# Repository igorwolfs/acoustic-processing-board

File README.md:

# acoustic-processing-hw
Repository for the main FPGA-processing board of my acoustic characterization device.

## Design goal
The goal of the board is to 
1. Measure analog signals amplified by a [pre-amplifier board](https://github.com/igorwolfs/acoustic-preamp-hw) for signals picked up from the piezo, at frequencies between 0.1 and 10 MHz. These analog signals are stored in RAM after measurement, processed on the FPGA and passed on.
2. Drive PWM signals for a [single-phase inverter-board](https://github.com/igorwolfs/acoustic-piezodriver-hw) connected to a piezo-element.

## Design constraints
Apart from technical constraints such as sampling rate (> 20 MHz), transfer / processing speed (10-bit x 35 MHz), etc... The main design constraint was keeping the price as low as possible.

## Stackup / Routing
6-layer stackup (JLC06161H-3313) with 
- L1, L6: controlled impedance layers.
	- 50 Ohm non-coplanar microstrip: 
		- TL Width (W): 0.157 mm 
		- Spacing between conductors: 2-3 x W
	- 100 Ohm differential non-coplanar
		- TL width (W): 0.122 mm
		- Diff-pair spacing: 0.2032 mm
		- Conductor spacing: 2-3 x W
- L4: power plane:
	- +2V5 Auxiliary FPGA voltage
	- +1V35 LPDDR3 voltage
	- +1V2 ETH voltage
	- +3V3 digital
	- +3V3 analog
- L2, L3, L5: GND planes
	- L2 (L1 reference)
	- L3 (L4 reference)
	- L5 (L6 reference)

### Rationale
Main reason for choosing a 6-layer over an 8-layer stack-up was price. Keeping LPDDR3-traces at appropriate impedance and matching delays proved to be a challenge with this layer count. Outcome to be judged after bringup.

## Main IC's
- Lattice EC5U-FPGA, with 25k LUT's.
- LPDDR3-RAM
- USB 33200-PHY (ULPI-bus)
- Ethernet PHY (RGMII interface)
- Analog frontend with MS9280 ADC in diff-mode, (fs <=35 MHz).

### Routing / Selection Rationale
#### Lattice ECP5U
The Lattice ECP5U was the best price-quality in terms of computing power. 

With a max CLK frequency of about 400 MHz it can operate around the lowest DDR3 speed class.

#### KSZ9031RN-Ethernet
Often used in open-source boards together with the ECP5U.

- RGMII interface operating at 125 MHz
- Differential pair needs to be tightly matched, offset calibration between pairs is performed.
- 4-pair RJ45 with intergrated magnetics (HR911130A)

#### Micron-DDR3 PHY
Anticipated was that around lower DDR3-speed classes (300 MHz, $\lambda = \frac{c}{300e6 * \sqrt{4.1}} = 50 cm$), delay-matching becomes less of an issue and higher ECP5U rise and fall times increase tolerance margin for the 50 ohm single-ended / 100 ohm differential impedance requirements.

- CMD-CTRL-bus 
	- signals led through vias twice.
	- CK+/- 42 mm
	- CMD/CTRL BUS signals kept around 35 mm (between 34-37 mm)
- DQU-group 
	- led through vias twice.
	- UDQS+/-: 21.7 mm
	- Data-signals kept within 1.5 mm
- DQL-group
	- signals kept on the first layer only.
	- LDQS+/-: 19.85 mm
	- Data-signals kept within 1.5 mm

 > References: [Orangecrab Board](https://github.com/orangecrab-fpga/orangecrab-hardware), Section 3.18 Lattice FPGA-DS-02012-3.2, [Micron DDR3 SDRAM](https://jlcpcb.com/api/file/downloadByFileSystemAccessId/8588894245961019392) table 58

#### USB3300-EZK
- ULPI-bus operating at 60 MHz
	- Traces were [delay-matched](docs/layout/USB/routing.md).
	- Impedance matched to 50 ohms.
- 2 Schmitt triggers were added for read-out of CC-line voltage to determine current USB PD capacity.

#### MS9280 ADC
Sampling rate > 2 times Nyquist, purchasing price was less than 1 $.

#### ADC RJ45 connectors + switch

2 RJ45 connectors meant to transfer analog signals attached with a switch. A comparison will be made for measuring analog signals between
- An RJ45 connector with internal magnetics.
- An RJ45 connector without magnetics, and with external blocking capacitors.
	- Capacitors might need to be changed, to stay out of S.R.F territory and limit phase-shift between differential signals.

#### W25Q128JVS SPI
2 external 128 MBit SPI IC's connected
- One to flash the ECP5U bitstream.
- One to flash firmware used in case of a soft-core CPU configured in the FPGA-fabric.

#### Other
More info on routing can be found in the (rather chaotic) [layout folder](docs/layout/) and [component selection folder](docs/schematic/component_selection/).

Simulations for ADI-devices can be found inside [ltspice-folder](simulations/ltspice/), TI-related sims can be found in the [TI-folder](simulations/TINA/)

## Booting
### Loading Bitstream 
2 possible ways of loading the bitstream of the ECP5U
- The JTAG-PMOD connector
- Flashing the external 128 MBit SPI connected to the startup MSPI of the ECP5U.

## Reviews
### Reddit
The first iteration of the design was placed on [reddit for review](https://www.reddit.com/r/PrintedCircuitBoard/comments/1m0hude/schematic_review_request_ecp5ufpga_board_with_hs/).

The initial design included longer trace-lengths to the DDR-PHY to achieve better delay and impedance matching. It was deemed that for the given stackup, sacrificing delay-budget and inter-trace distance wasn't worth the increase in trace lengths at those frequencies.

<table>
  <tr>
    <th>Before</th>
    <th>After</th>
  <tr>
    <td> </td>
    <td></td>
   </tr> 
   <tr>
      <td></td>
      <td>
  </td>
</tr>
</table>

### Other
An additional LC-filter was added between shield and ground mostly for ESD-reasons.

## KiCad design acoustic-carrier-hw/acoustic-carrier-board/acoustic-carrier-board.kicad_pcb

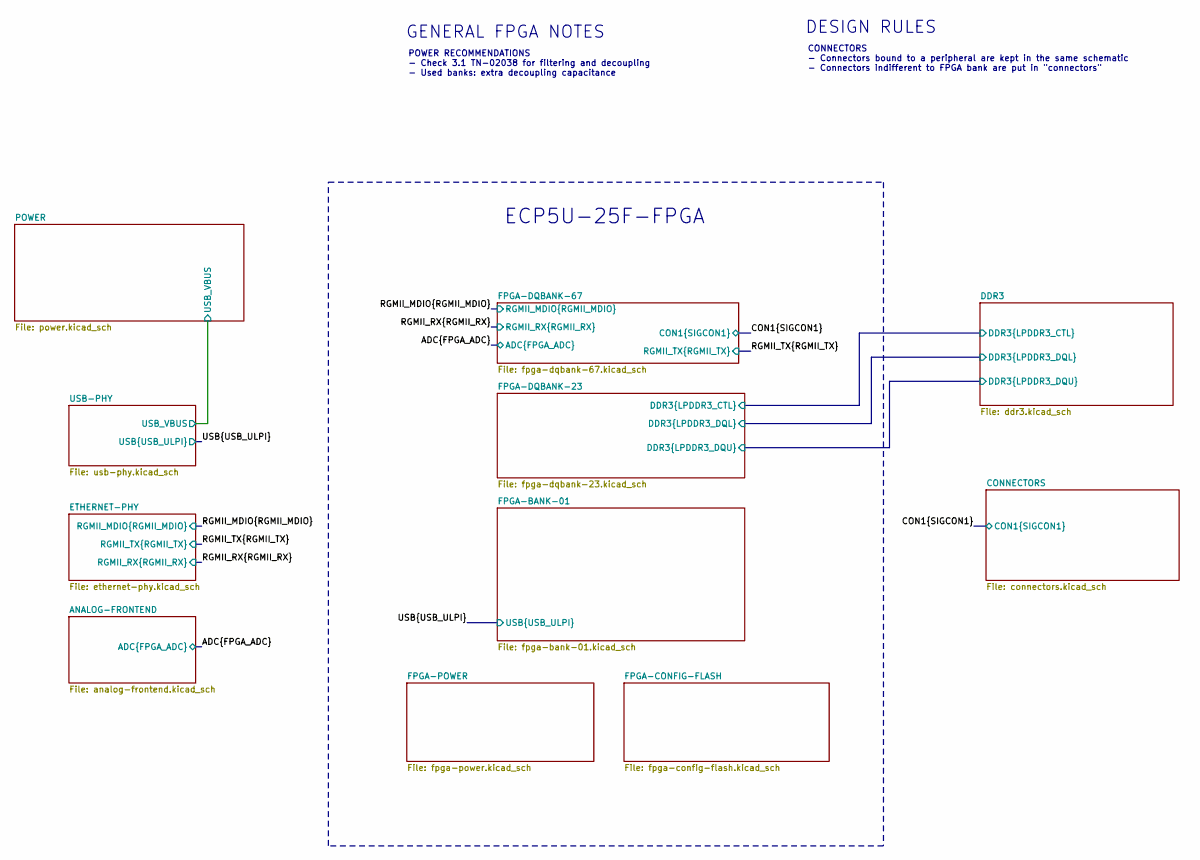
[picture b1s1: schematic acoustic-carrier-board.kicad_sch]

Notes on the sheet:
GENERAL FPGA NOTES
ECP5U-25F-FPGA
POWER RECOMMENDATIONS - Check 3.1 TN-02038 for filtering and decoupling - Used banks: extra decoupling capacitance
CONNECTORS - Connectors bound to a peripheral are kept in the same schematic - Connectors indifferent to FPGA bank are put in "connectors"
DESIGN RULES

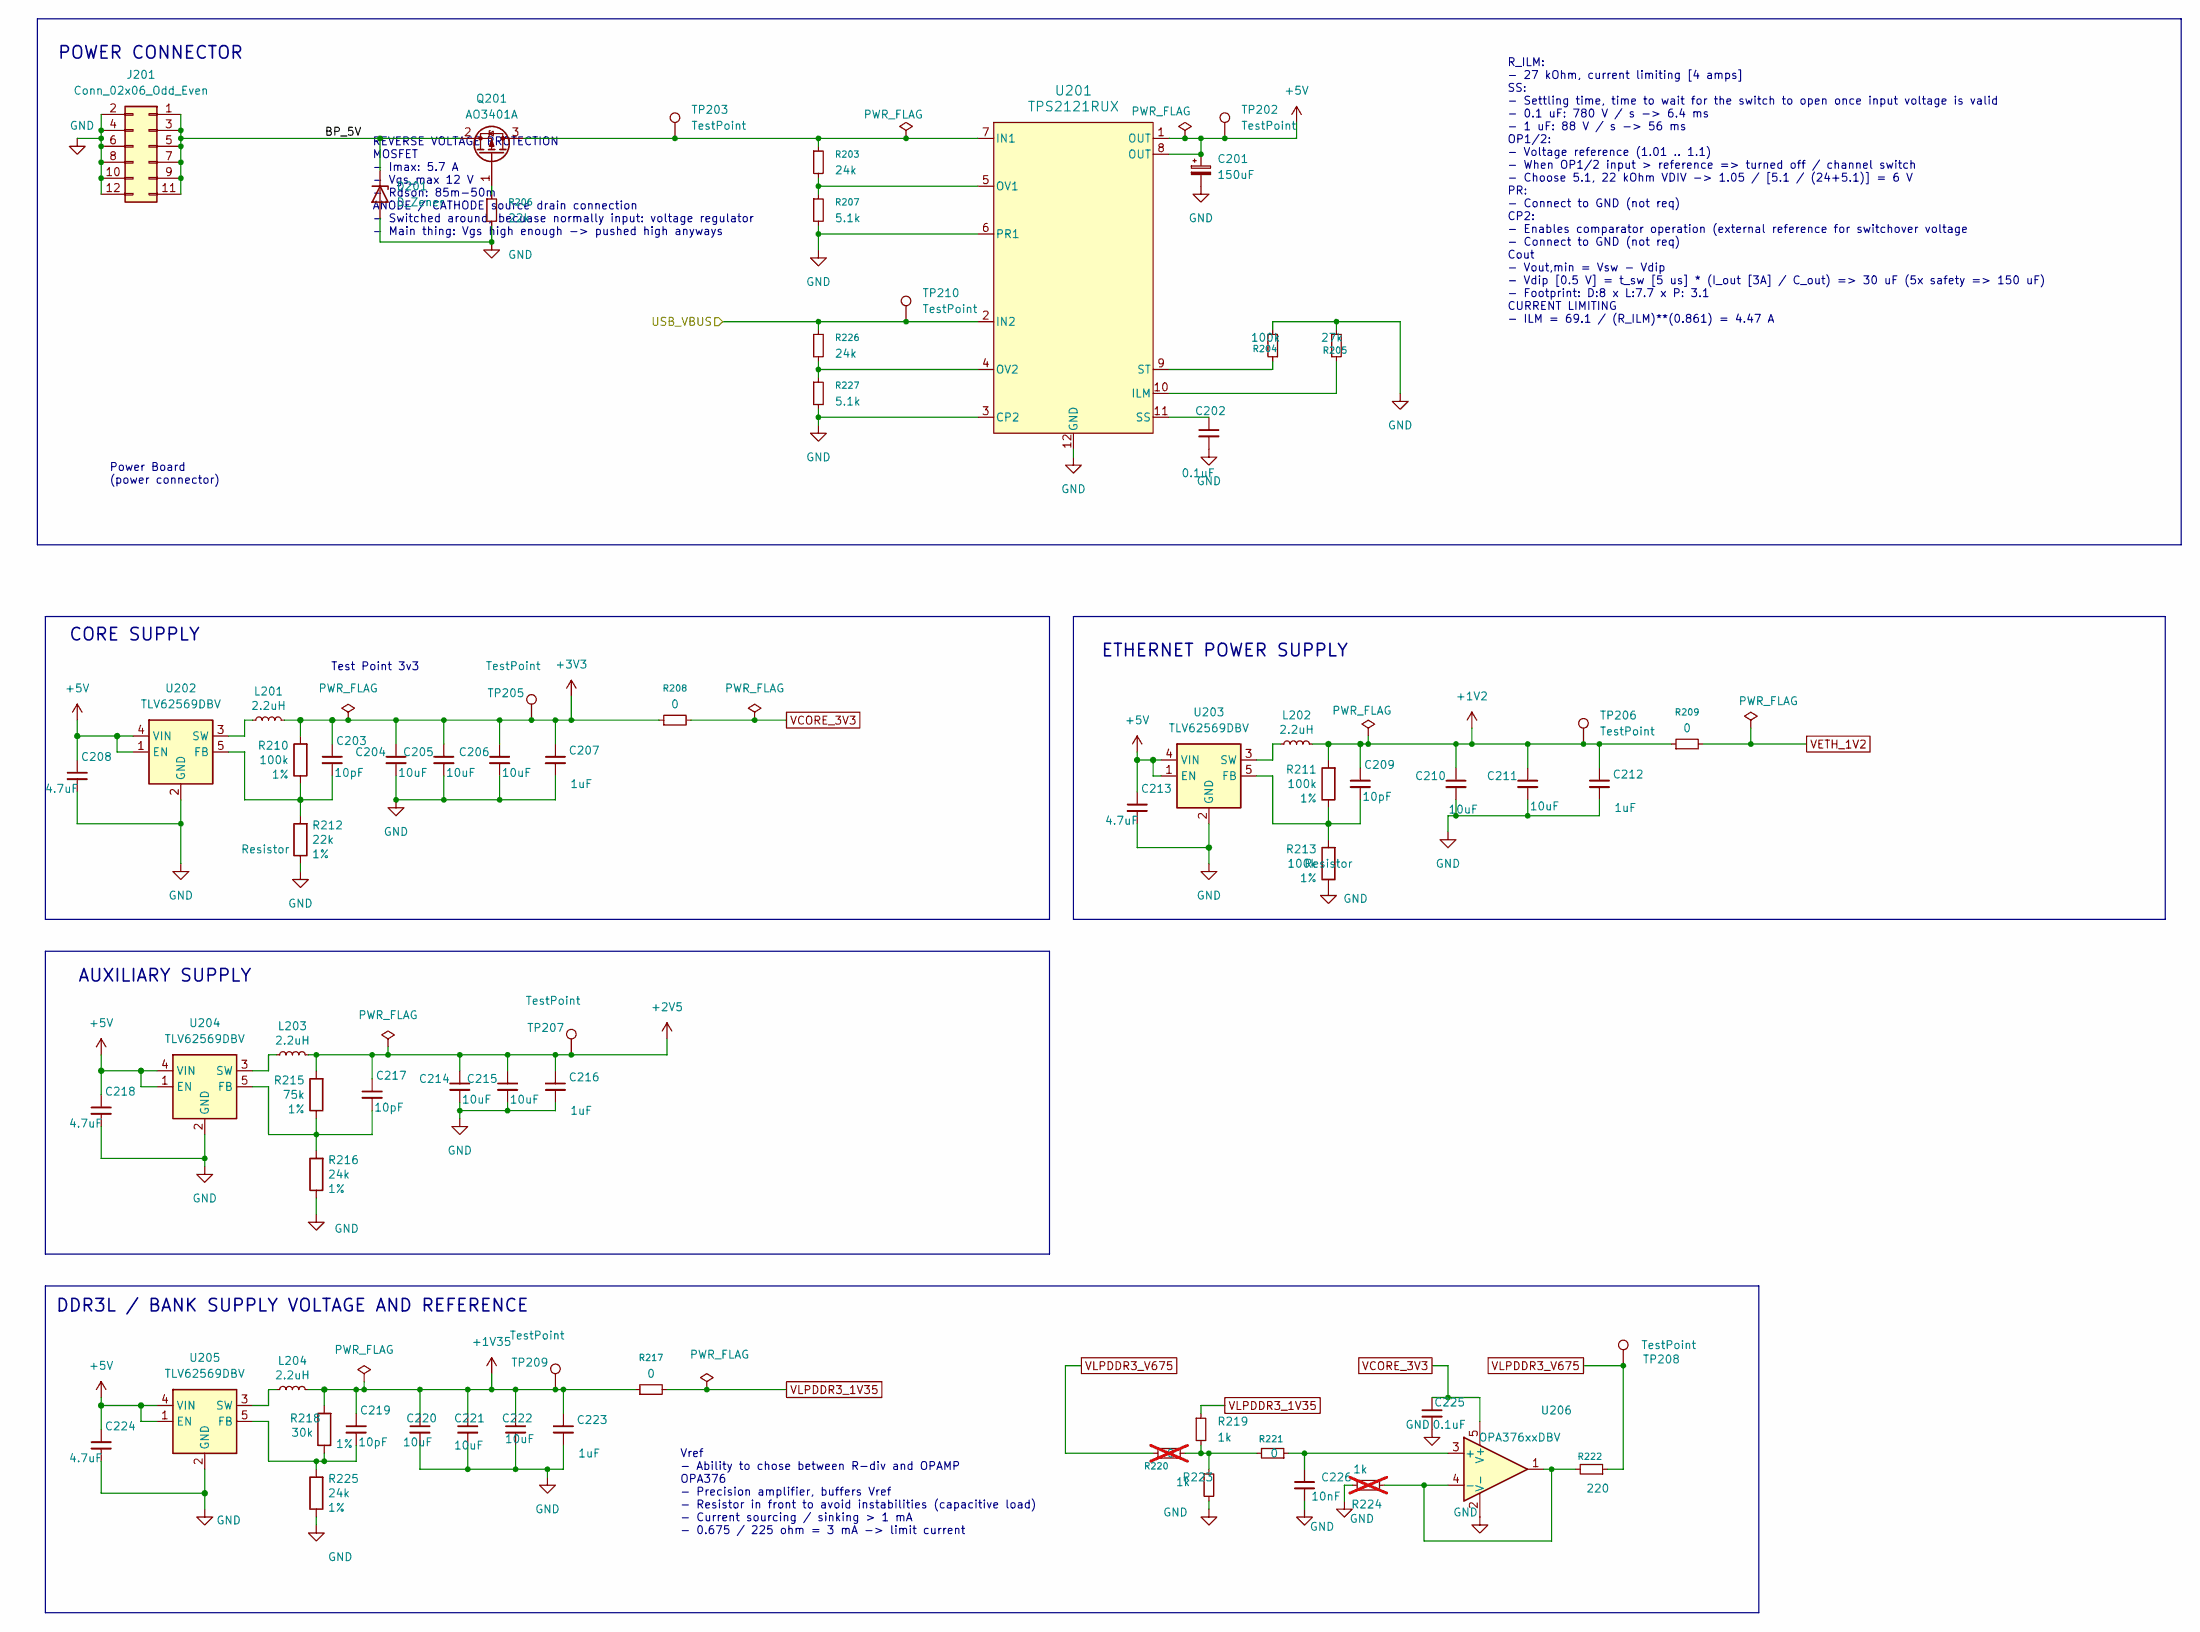
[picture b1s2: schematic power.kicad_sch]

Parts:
C201: 150uF; CP_Elec_8x6.2; MPN APXE160ARA151MH80G
C202, C225: 0.1uF; C_0201_0603Metric; MPN CGA0201X7R104K160ET
C203, C209, C217, C219: 10pF; C_0402_1005Metric; MPN CL05C100JB5NNNC
C204, C205, C206, C210, C211, C214, C215, C220, C221, C222: 10uF; C_0603_1608Metric; MPN CL10A106KP8NNNC
C207, C212, C216, C223: 1uF; C_0805_2012Metric; MPN CL21B105KBFNNNE
C208, C213, C218, C224: 4.7uF; C_0402_1005Metric; MPN CL05A475MP5NRNC
C226: 10nF; C_0201_0603Metric; MPN 0201B103K250NT
D201: D_Zener; D_SOD-323_HandSoldering; MPN BZT52C6V8S
J201: Conn_02x06_Odd_Even; PinSocket_2x06_P2.54mm_Horizontal; MPN PM254-2-06-W-8.5
L201, L202, L203, L204: 2.2uH; L_Changjiang_FNR4018S; MPN NR4018S2R2MT
Q201: AO3401A; SOT-23; MPN AO3401A
R203, R216, R225, R226: 24k; R_0603_1608Metric; MPN 0603WAF2402T5E
R204: 100k; R_0603_1608Metric_Pad0.98x0.95mm_HandSolder; MPN 0603WAF1003T5E
R205: 27k; R_0603_1608Metric; MPN 0603WAF2702T5E
R206, R212: 22k; R_0603_1608Metric; MPN 0603WAF2202T5E
R207, R227: 5.1k; R_0603_1608Metric; MPN 0603WAF5101T5E
R208, R209, R217: 0; R_0805_2012Metric_Pad1.20x1.40mm_HandSolder; MPN 0805W8F0000T5E
R210, R211, R213: 100k; R_0603_1608Metric; MPN 0603WAF1003T5E
R215: 75k; R_0603_1608Metric; MPN 0603WAF7502T5E
R218: 30k; R_0603_1608Metric; MPN 0603WAF3002T5E
R219, R223: 1k; R_0603_1608Metric; MPN 0603WAF1001T5E
R220: 0; R_0603_1608Metric; MPN 0603WAF0000T5E; not fitted
R221: 0; R_0603_1608Metric; MPN 0603WAF0000T5E
R222: 220; R_0603_1608Metric; MPN 0603WAF2200T5E
R224: 1k; R_0603_1608Metric; MPN C21190; not fitted
TP202, TP203, TP205, TP206, TP207, TP208, TP209, TP210: TestPoint; TestPoint_Loop_D1.80mm_Drill1.0mm_Beaded
U201: TPS2121RUX; TPS2121; MPN TPS2121RUXT
U202, U203, U204, U205: TLV62569DBV; SOT-23-5; MPN TLV62569DBVR
U206: OPA376xxDBV; SOT-23-5; MPN OPA376AIDBVR

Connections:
+1V2: C209.1, C210.1, C211.1, C212.1, L202.2, R209.1, R211.2, TP206.1
+1V35: C219.1, C220.1, C221.1, C222.1, C223.1, L204.2, R217.1, R218.2, TP209.1
+2V5: C214.1, C215.1, C216.1, C217.1, L203.2, R215.2, TP207.1; also elsewhere on the board
+3V3: C203.1, C204.1, C205.1, C206.1, C207.1, L201.2, R208.1, R210.2, TP205.1
+5V: C201.1, C208.1, C213.1, C218.1, C224.1, TP202.1, U201.1 (OUT), U201.8 (OUT), U202.1 (EN), U202.4 (VIN), U203.1 (EN), U203.4 (VIN), U204.1 (EN), U204.4 (VIN), U205.1 (EN), U205.4 (VIN)
/POWER/BP_5V: D201.1 (K), J201.1, J201.3, J201.5, J201.7, J201.9, J201.11, Q201.2 (S)
/POWER/USB_VBUS: R226.1, TP210.1, U201.2 (IN2); also elsewhere on the board
GND: C201.2, C202.2, C204.2, C205.2, C206.2, C207.2, C208.2, C210.2, C211.2, C212.2, C213.2, C214.2, C215.2, C216.2, C218.2, C220.2, C221.2, C222.2, C223.2, C224.2, C225.2, C226.2, D201.2 (A), J201.2, J201.4, J201.6, J201.8, J201.10, J201.12, R204.2, R205.1, R206.2, R207.2, R212.1, R213.1, R216.1, R223.2, R224.1, R225.1, R227.2, U201.3 (CP2), U201.6 (PR1), U201.12 (GND), U202.2 (GND), U203.2 (GND), U204.2 (GND), U205.2 (GND), U206.2 (V-); also elsewhere on the board
unnamed: Q201.3 (D), R203.1, TP203.1, U201.7 (IN1)
unnamed: Q201.1 (G), R206.1
unnamed: R219.2, R220.1, R221.2, R223.1
unnamed: R205.2, U201.10 (ILM)
unnamed: R203.2, R207.1, U201.5 (OV1)
unnamed: R226.2, R227.1, U201.4 (OV2)
unnamed: C202.1, U201.11 (SS)
unnamed: R204.1, U201.9 (ST)
unnamed: C203.2, R210.1, R212.2, U202.5 (FB)
unnamed: L201.1, U202.3 (SW)
unnamed: C209.2, R211.1, R213.2, U203.5 (FB)
unnamed: L202.1, U203.3 (SW)
unnamed: C217.2, R215.1, R216.2, U204.5 (FB)
unnamed: L203.1, U204.3 (SW)
unnamed: C219.2, R218.1, R225.2, U205.5 (FB)
unnamed: L204.1, U205.3 (SW)
unnamed: C226.1, R221.1, U206.3 (+)
unnamed: R222.2, R224.2, U206.1, U206.4 (-)
VCORE_3V3: C225.1, R208.2, U206.5 (V+); also elsewhere on the board
VETH_1V2: R209.2; also elsewhere on the board
VLPDDR3_1V35: R217.2, R219.1; also elsewhere on the board
VLPDDR3_V675: R220.2, R222.1, TP208.1; also elsewhere on the board

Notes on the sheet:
R_ILM: - 27 kOhm, current limiting [4 amps] SS: - Settling time, time to wait for the switch to open once input voltage is valid - 0.1 uF: 780 V / s -> 6.4 ms - 1 uF: 88 V / s -> 56 ms OP1/2: - Voltage reference (1.01 .. 1.1) - When OP1/2 input > reference => turned off / channel switch - Choose 5.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
Test Point 3v3
DDR3L / BANK SUPPLY VOLTAGE AND REFERENCE
Power Board (power connector)
POWER CONNECTOR
ETHERNET POWER SUPPLY
REVERSE VOLTAGE PROTECTION MOSFET - Imax: 5.7 A - Vgs_max 12 V - Rdson: 85m-50m ANODE / CATHODE source drain connection - Switched around, becuase normally input: voltage regulator - Main thing: Vgs high enough -> pushed high anyways
Vref - Ability to chose between R-div and OPAMP OPA376 - Precision amplifier, buffers Vref - Resistor in front to avoid instabilities (capacitive load) - Current sourcing / sinking > 1 mA - 0.675 / 225 ohm = 3 mA -> limit current
CORE SUPPLY
AUXILIARY SUPPLY

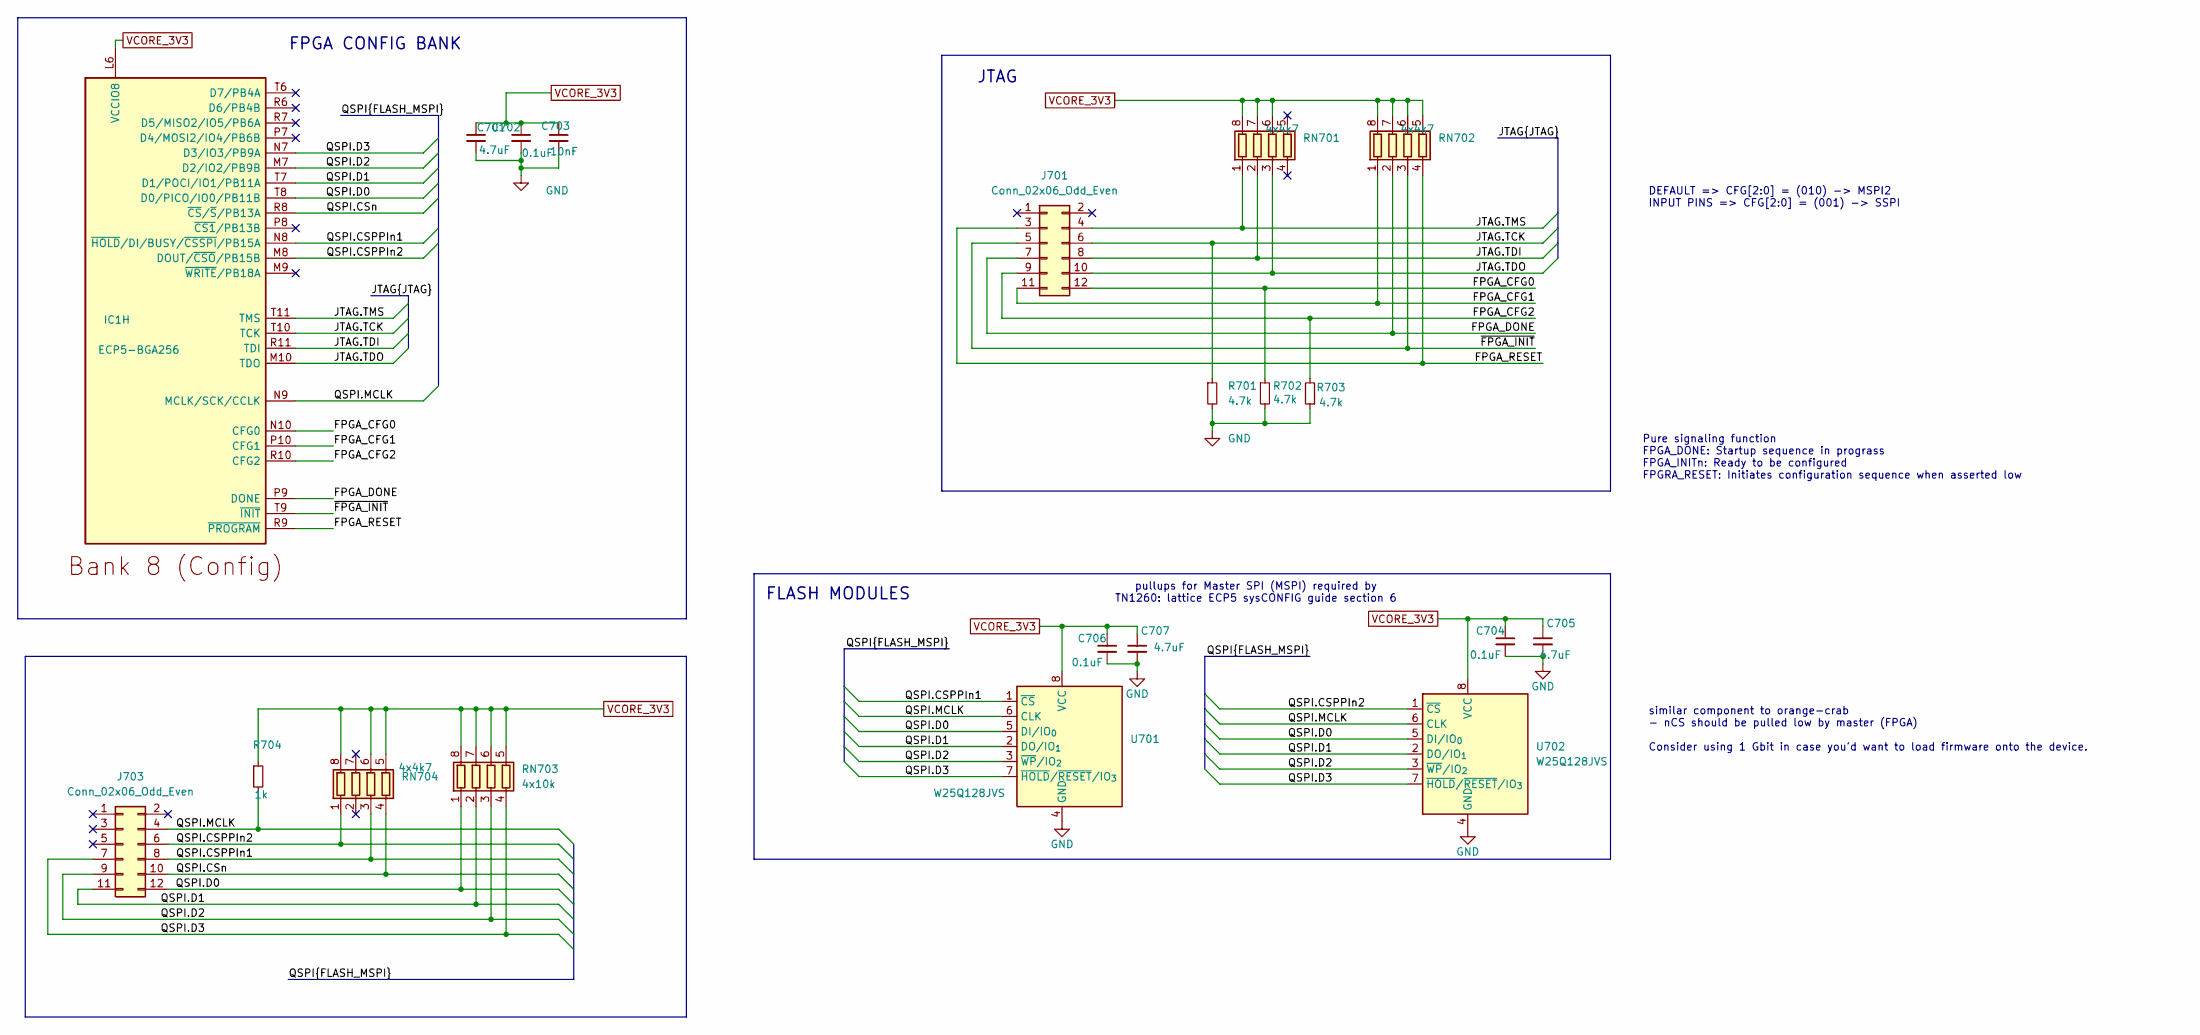
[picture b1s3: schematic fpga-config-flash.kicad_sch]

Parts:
C701, C705, C707: 4.7uF; C_0402_1005Metric; MPN CL05A475MP5NRNC
C702, C704, C706: 0.1uF; C_0201_0603Metric; MPN CGA0201X7R104K160ET
C703: 10nF; C_0201_0603Metric; MPN 0201B103K250NT
IC1: ECP5-BGA256; BGA256C80P16X16_1400X1400X170; MPN LFE5U-25F-6BG256C
J701, J703: Conn_02x06_Odd_Even; PinSocket_2x06_P2.54mm_Horizontal; MPN PM254-2-06-W-8.5
R701, R702, R703: 4.7k; R_0402_1005Metric; MPN 0402WGF4701TCE
R704: 1k; R_0402_1005Metric; MPN 0402WGF1001TCE
RN701, RN702, RN704: 4x4k7; R_Array_Convex_4x0603; MPN 4D03WGJ0472T5E
RN703: 4x10k; R_Array_Convex_4x0603; MPN 4D03WGJ0103T5E
U701, U702: W25Q128JVS; SOIC-8_5.3x5.3mm_P1.27mm; MPN W25Q128JVSIQ

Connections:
/FPGA-CONFIG-FLASH/FPGA_CFG0: IC1.N10 (CFG0), J701.12, R702.1
/FPGA-CONFIG-FLASH/FPGA_CFG1: IC1.P10 (CFG1), J701.11, RN702.1 (R1.1)
/FPGA-CONFIG-FLASH/FPGA_CFG2: IC1.R10 (CFG2), J701.9, R703.2
/FPGA-CONFIG-FLASH/FPGA_DONE: IC1.P9 (DONE), J701.7, RN702.2 (R2.1)
/FPGA-CONFIG-FLASH/FPGA_RESET: IC1.R9 (~PROGRAM), J701.3, RN702.4 (R4.1)
/FPGA-CONFIG-FLASH/JTAG.TCK: IC1.T10 (TCK), J701.6, R701.1
/FPGA-CONFIG-FLASH/JTAG.TDI: IC1.R11 (TDI), J701.8, RN701.2 (R2.1)
/FPGA-CONFIG-FLASH/JTAG.TDO: IC1.M10 (TDO), J701.10, RN701.3 (R3.1)
/FPGA-CONFIG-FLASH/JTAG.TMS: IC1.T11 (TMS), J701.4, RN701.1 (R1.1)
/FPGA-CONFIG-FLASH/QSPI.CSPPIn1: IC1.N8 (~HOLD/DI/BUSY/~CSSPI/PB15A), J703.8, RN704.3 (R3.1), U701.1 (~CS)
/FPGA-CONFIG-FLASH/QSPI.CSPPIn2: IC1.M8 (DOUT/~CSO/PB15B), J703.6, RN704.1 (R1.1), U702.1 (~CS)
/FPGA-CONFIG-FLASH/QSPI.CSn: IC1.R8 (~CS/~S/PB13A), J703.10, RN704.4 (R4.1)
/FPGA-CONFIG-FLASH/QSPI.D0: IC1.T8 (D0/PICO/IO0/PB11B), J703.12, RN703.1 (R1.1), U701.5 (DI/IO_{0}), U702.5 (DI/IO_{0})
/FPGA-CONFIG-FLASH/QSPI.D1: IC1.T7 (D1/POCI/IO1/PB11A), J703.11, RN703.2 (R2.1), U701.2 (DO/IO_{1}), U702.2 (DO/IO_{1})
/FPGA-CONFIG-FLASH/QSPI.D2: IC1.M7 (D2/IO2/PB9B), J703.9, RN703.3 (R3.1), U701.3 (~WP/IO_{2}), U702.3 (~WP/IO_{2})
/FPGA-CONFIG-FLASH/QSPI.D3: IC1.N7 (D3/IO3/PB9A), J703.7, RN703.4 (R4.1), U701.7 (~HOLD/~RESET/IO_{3}), U702.7 (~HOLD/~RESET/IO_{3})
/FPGA-CONFIG-FLASH/QSPI.MCLK: IC1.N9 (MCLK/SCK/CCLK), J703.4, R704.2, U701.6 (CLK), U702.6 (CLK)
/FPGA-CONFIG-FLASH/~FPGA_INIT: IC1.T9 (~INIT), J701.5, RN702.3 (R3.1)
GND: C701.2, C702.2, C703.2, C704.2, C705.2, C706.2, C707.2, R701.2, R702.2, R703.1, U701.4 (GND), U702.4 (GND); also elsewhere on the board
VCORE_3V3: C701.1, C702.1, C703.1, C704.1, C705.1, C706.1, C707.1, IC1.L6 (VCCIO8), R704.1, RN701.6 (R3.2), RN701.7 (R2.2), RN701.8 (R1.2), RN702.5 (R4.2), RN702.6 (R3.2), RN702.7 (R2.2), RN702.8 (R1.2), RN703.5 (R4.2), RN703.6 (R3.2), RN703.7 (R2.2), RN703.8 (R1.2), RN704.5 (R4.2), RN704.6 (R3.2), RN704.8 (R1.2), U701.8 (VCC), U702.8 (VCC); also elsewhere on the board

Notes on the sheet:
JTAG
similar component to orange-crab - nCS should be pulled low by master (FPGA) Consider using 1 Gbit in case you'd want to load firmware onto the device.
DEFAULT => CFG[2:0] = (010) -> MSPI2 INPUT PINS => CFG[2:0] = (001) -> SSPI
Pure signaling function FPGA_DONE: Startup sequence in prograss FPGA_INITn: Ready to be configured FPGRA_RESET: Initiates configuration sequence when asserted low
pullups for Master SPI (MSPI) required by TN1260: lattice ECP5 sysCONFIG guide section 6
FLASH MODULES
FPGA CONFIG BANK

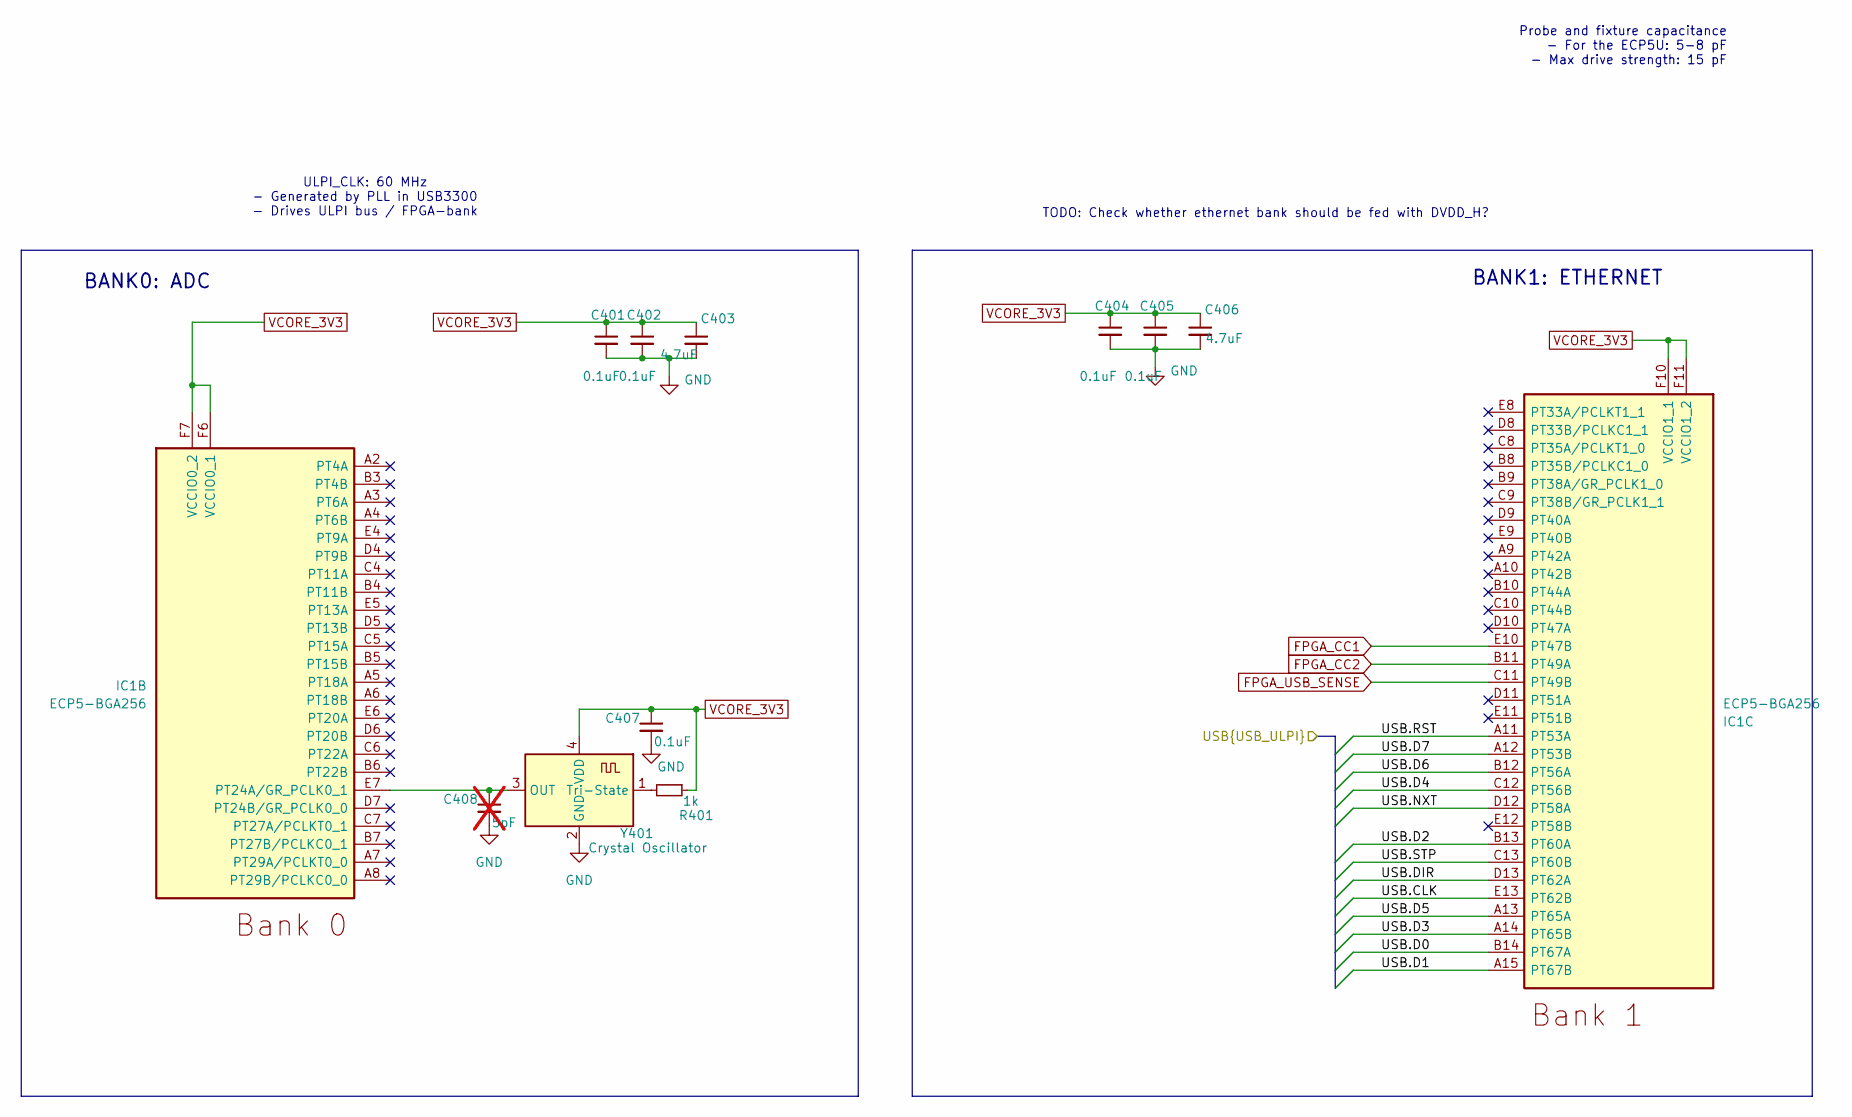
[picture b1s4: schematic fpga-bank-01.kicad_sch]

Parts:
C401, C402, C404, C405, C407: 0.1uF; C_0201_0603Metric; MPN CGA0201X7R104K160ET
C403, C406: 4.7uF; C_0402_1005Metric; MPN CL05A475MP5NRNC
C408: 5pF; C_0603_1608Metric; not fitted
IC1: ECP5-BGA256; BGA256C80P16X16_1400X1400X170; MPN LFE5U-25F-6BG256C
R401: 1k; R_0603_1608Metric; MPN 0603WAF1001T5E
Y401: Crystal Oscillator; Crystal_SMD_3225-4Pin_3.2x2.5mm; MPN O93225100MEDA4SI-13

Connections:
/USB.CLK: IC1.E13 (PT62B); also elsewhere on the board
/USB.D0: IC1.B14 (PT67A); also elsewhere on the board
/USB.D1: IC1.A15 (PT67B); also elsewhere on the board
/USB.D2: IC1.B13 (PT60A); also elsewhere on the board
/USB.D3: IC1.A14 (PT65B); also elsewhere on the board
/USB.D4: IC1.C12 (PT56B); also elsewhere on the board
/USB.D5: IC1.A13 (PT65A); also elsewhere on the board
/USB.D6: IC1.B12 (PT56A); also elsewhere on the board
/USB.D7: IC1.A12 (PT53B); also elsewhere on the board
/USB.DIR: IC1.D13 (PT62A); also elsewhere on the board
/USB.NXT: IC1.D12 (PT58A); also elsewhere on the board
/USB.RST: IC1.A11 (PT53A); also elsewhere on the board
/USB.STP: IC1.C13 (PT60B); also elsewhere on the board
FPGA_CC1: IC1.E10 (PT47B); also elsewhere on the board
FPGA_CC2: IC1.B11 (PT49A); also elsewhere on the board
FPGA_USB_SENSE: IC1.C11 (PT49B); also elsewhere on the board
GND: C401.2, C402.2, C403.2, C404.2, C405.2, C406.2, C407.2, C408.2, Y401.2 (GND); also elsewhere on the board
unnamed: C408.1, IC1.E7 (PT24A/GR_PCLK0_1), Y401.3 (OUT)
unnamed: R401.2, Y401.1 (Tri-State)
VCORE_3V3: C401.1, C402.1, C403.1, C404.1, C405.1, C406.1, C407.1, IC1.F6 (VCCIO0_1), IC1.F7 (VCCIO0_2), IC1.F10 (VCCIO1_1), IC1.F11 (VCCIO1_2), R401.1, Y401.4 (VDD); also elsewhere on the board

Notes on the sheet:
Probe and fixture capacitance - For the ECP5U: 5-8 pF - Max drive strength: 15 pF
BANK1: ETHERNET
TODO: Check whether ethernet bank should be fed with DVDD_H?
BANK0: ADC
ULPI_CLK: 60 MHz - Generated by PLL in USB3300 - Drives ULPI bus / FPGA-bank
